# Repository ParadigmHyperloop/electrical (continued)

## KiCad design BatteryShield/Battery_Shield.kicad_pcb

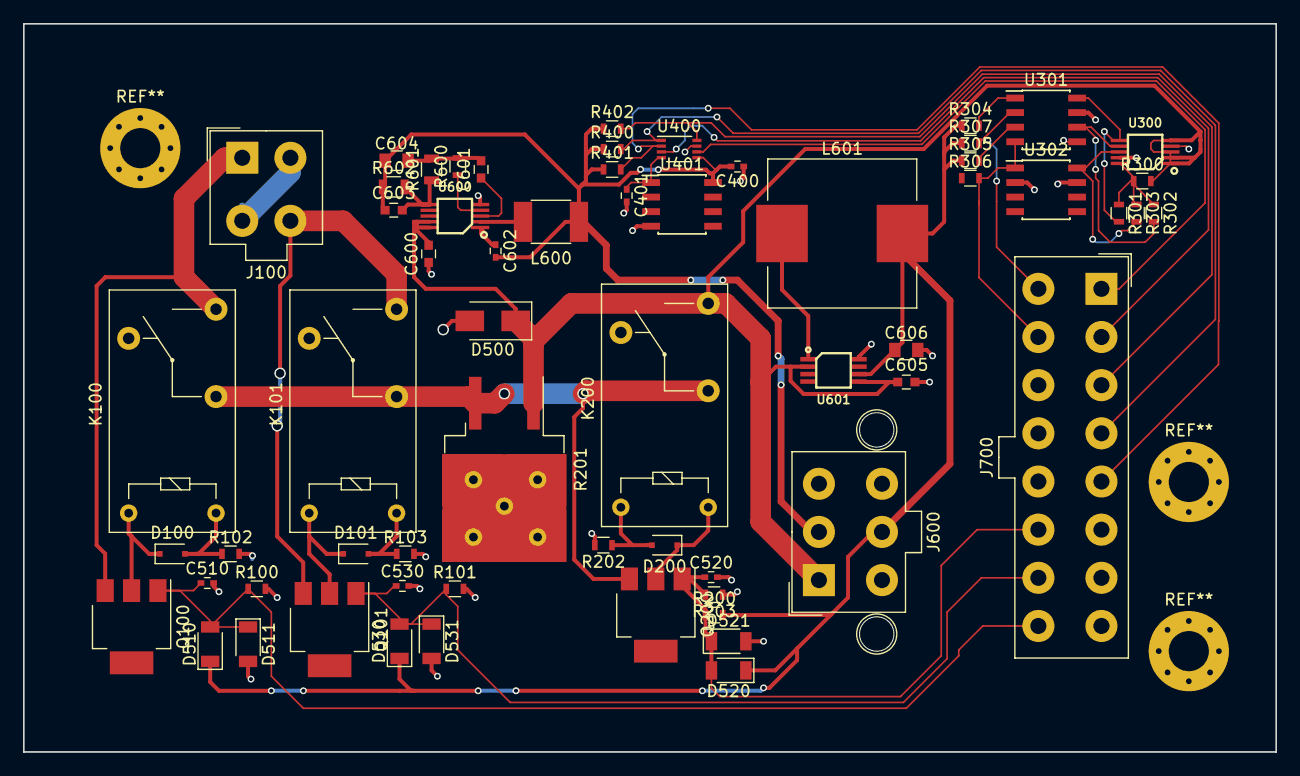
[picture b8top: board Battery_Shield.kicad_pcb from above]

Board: 2 copper layers, 109.2 x 63.5 mm, 62 parts (0 on the bottom side), 38 nets.

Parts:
C400: .1u; C_0402
C401: 10n; C_0402
C510, C520, C530: 10nF; C_0402
C600: 4.7uF; C_0603
C601, C605: 1uF; C_0603
C602: .1uF; C_0402
C603: 10pF; C_0603
C604: 22uF; C_0805
C606: 10uF; C_0805
D100, D101, D200: D; D_SOD-323F
D500: SMAJ36CA; D_SMA
D510, D511, D520, D521, D530, D531: DZ2W03600L; D_1206
J100: Conn_02x02_Counter_Clockwise; Molex_MiniFit-JR-5556-04A_2x02x4.20mm_Straight
J600: Conn_02x03_Counter_Clockwise; Molex_MiniFit-JR-5556-06B_2x03x4.20mm_Straight
J700: MOLEX-MINIFIT-JR-5556; Molex_MiniFit-JR-5556-16A_2x08x4.20mm_Straight
K100, K101, K200: G5LE-14 DC3; Relay_SPDT_OMRON-G5Q
L600: 2.2uH; L_1812
L601: 150uH; L_Wuerth_HCI-1350
Q100, Q101, Q200: ZVP4525G; SOT-223
R100, R101, R102, R103, R200, R202, R203, R400, R401, R402: 1k; R_0603
R201: powerRes; TO-263-2
R300: 0.02; R_0603
R301, R302, R303, R600: 18.2k; R_0603
R304, R305: 0.51k; R_0603
R306, R307: 10k; R_0603
R601: 187K; R_0805
R602: 1M; R_0805
U300: LTC4151IMS-1; MSOP10
U301, U302: MOCD207M; SOIC-8_3.9x4.9mm_Pitch1.27mm
U400: ADC081C021; VSSOP-8_2.3x2mm_Pitch0.5mm
U401: LM35-D; SOIC-8_3.9x4.9mm_Pitch1.27mm
U600: LT8608; MSOP10
U601: LTC3642-3.3; MSOP8

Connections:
3.3V_REG: C606.1, D510.1, D520.1, D530.1, J600.5, L601.2, R200.2, R304.1, R305.1, R306.1, R307.1, U601.6
5V_REG: C400.2, C602.2, C603.1, C604.1, J600.2, L600.1, R400.1, R401.1, R402.1, R602.1, U400.5, U401.8
BBB_GND: C400.1, C401.2, C510.2, C520.2, C530.2, C600.1, C605.2, C606.2, D500.2, D511.2, D521.2, D531.2, J600.3, J600.4, J600.6, J700.6, J700.7, J700.8, J700.11, J700.12, J700.13, R100.2, R101.2, R102.2, R103.2, R202.2, R203.1, U300.4, U300.9, U301.5, U301.7, U302.2, U302.7, U400.7, U401.4, U600.5, U601.8
CV_SCL_BBB: J700.9, R307.2, U301.2
CV_SDA_BBB: J700.10, R306.2, U301.4, U302.1
unnamed: C401.1, U400.4, U401.1
unnamed: C601.1, U600.3
unnamed: C601.2, C604.2, R600.2, R601.2
unnamed: C602.1, U600.1
unnamed: C603.2, R601.1, R602.2, U600.6
unnamed: D100.1, K100.5, Q100.2
unnamed: D100.2, K100.1, R102.1
unnamed: D101.1, K101.5, Q101.2
unnamed: D101.2, K101.1, R103.1
unnamed: D200.1, K200.1, Q200.2
unnamed: D200.2, K200.5, R202.1
unnamed: J100.1, K100.3, Q100.3
unnamed: J100.2, J100.3
unnamed: J100.4, K101.3, Q101.3
unnamed: L600.2, U600.2
unnamed: L601.1, U601.1
unnamed: R300.1, R301.1, R302.1, R303.1, U300.10
unnamed: R301.2, U300.6, U301.8
unnamed: R302.2, U300.7, U301.6
unnamed: R303.2, U300.8, U302.8
unnamed: R304.2, U301.1
unnamed: R305.2, U301.3
unnamed: R600.1, U600.4
PACK_A_ON_N: C510.1, D510.2, D511.1, J700.16, Q100.1, R100.1
PACK_B_ON_N: C530.1, D530.2, D531.1, J700.15, Q101.1, R101.1
PRECHARGE_N: C520.1, D520.2, D521.1, J700.14, Q200.1, R200.1, R203.2
TEMP_DIN_BBB: J700.5, R401.2, U400.2
TEMP_SCL_BBB: J700.4, R400.2, U400.1
TEMP_SDA_BBB: J700.3, R402.2, U400.8
TEMP_SLAVE_ADDR0: J700.2, U400.3
TEMP_SLAVE_ADDR1: J700.1, U400.6
V_BATT37: C600.2, C605.1, D500.1, J600.1, K200.3, R201.1, R300.2, U300.1, U300.2, U300.3, U300.5, U600.9, U600.10, U601.2, U601.5
V_BATT37_PC: K100.2, K101.2, K200.2, Q200.3, R201.3

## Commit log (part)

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2016-12-23 LED Board
    Added the updated LED board with a fairly final PCB layout. It also contains the conditioning circuit for merkl's board for the PSI indicator because there is no more room on his board.
2016-12-26 Revised dimensions of Battery Board to 2.5in x 5.5in. Began layout mostly from scratch because previous revision was not good.
2016-12-27 Completed layout for Battery Board. TODO: DFM Checks
2016-12-28 Committing changes from Luke on MotherBoard
2016-12-31 Full Motherboard Rev1 -- sent for fab
2016-12-31 Minor changes to EmergencyBoard
2017-01-02 Add Correct Motherboard to git
2017-01-03 Finished schematic for SolidStateRelayBoard
2017-01-04 Completed most of layout for SSR board.
2017-01-08 Updated battery board and SSR Board. Completed schematic and layout for Pusher Protection Board (and also renamed it from Emergency Board).
2017-01-08 Corrected problem with Pusher Protection Board. Updated both schematic and layout and regenerated and zipped Gerbers. Ready for fab.
2017-01-12 Motherboard R 1-2
2017-01-12 added Gerbers
2017-01-12 Gerbers should be here now
2017-01-18 Forgot some digikey P/N s
2017-03-29 Tutorial up to board layout complete...Proofread 3/29/2017
2017-04-17 Updated Root Layout Schematic
    - Changed the layout to a modular design like the newer schematics.
    - Added 9th 24V Rail
    - Added 2nd 5v Rail
2017-05-02 Adding Changes to the SSR Board such as a change on the PCB allocating for the correct amount of channels as well as adding the control circuitry for the MPYE’s to the schematic. So changes on the: s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
2017-05-08 Added the LED driver IC to the schematic and started making the changes necessary to the PCB
2017-05-10 Fixed grounding of bat output and connected missing ground connection on LTC chip
2017-05-17 Added the xtr117 to the schematic but I still need to make the footprint for it since the one on kicad is wrong.
2017-05-17 changed to ppm
2017-05-17 Small Misc Changes
2017-05-27 Updated THBO to Rev2
    -Split the board into two parts to allow for better placement on the
    pod.
    -Added LEDs to 5V line
    -Added pin headers at the input terminals to easily put the board into
    self-reference mode using jumpers
    -Changed Vref from 0.64V to 1.25V
2017-05-29 SSR Board
    Misc small changes
2017-05-29 SSR Board
    Small changes to PCB
2017-05-30 SSR Board
    Added Part numbers and links
2017-05-31 MotherfuckingEE
2017-06-02 Made Changes to LED board and SSR
    Added different 5V regulators and polished SSR
2017-06-12 THBO BOM Update, MPB GPIO Schematic
    THBO
    - Updated a few componets parameter values for BOM
    - Created BOM for the board
    MPB
    - Created Schematic for GPIO Circuit to control regulators
2017-06-13 Moving along
2017-06-20 Silk screen mods
2017-06-23 Made a Print
    Just made a PDF
2017-06-27 Added gerbers for THBO
2017-06-28 Updated Silkscreens and added BBB_INT to J106
2017-07-06 Final edits -- awaiting review before sending out
2017-07-06 computer is dying
2017-07-07 XTR111
    Added the xtr111 circuit
2017-07-09 Big Changes to the SSR Board
    Almost finished with the SSR Board. Added the xtr 111 circuits and made
    the layout much cleaner.
2017-07-09 small change on pcb
    mounting holes were messed up
2017-07-10 Finished SSR Board rev 2.1.1
    Updatessss
2017-07-10 weird saved file
2017-07-10 Small Changes
2017-07-10 Small changes to SSR
    Merkl Pls Look
2017-07-11 Rev 2 of battery boards: includes a current sense resistor, pre-charge FET w/ timer, and main FET w/ timer
2017-07-11 Made new Gerbers and PDFs
2017-07-13 Ed please help
2017-07-13 Finished adding footprints; roughly placed all components
2017-07-14 Fixed minor error in Main FET timing circuit
2017-07-15 Updated silkscreen; optimized current consumption; added subcircuit simulations
2017-07-15 Cleaned up some routing; generated Gerbers
2017-07-17 Fixed component footprints; finalized silkscreen; output Gerbers
2017-07-24 Final BOM
2017-07-26 Added the Final BOM
2017-07-26 Initial Changes to LED Board
2017-07-27 Changes as pef discussed with Chris
2017-07-29 Added changes as per Chris requests
2017-07-29 Updated 1M resistors to 2M based on component availability
2017-07-30 Pushing up James' changes
2017-07-30 Adding docs
2017-07-31 Added Digikey PN and Mfg. PN
2017-08-02 Mobo Version 2.1 Added Silk scren Ground Plane Cleanup Pinout changes on Beaglebone Headers, need to modify cabeling from V2.0 and earlier Added power sequencing for ADCs Removed Y3 ADC Removed TI Ba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
2017-08-03 comitted a git sin. thx matan
2017-08-04 Updating to kiCAD version 4.0.6. Updated some .drl files per advanced circuits hold order
2017-08-14 Changed op amp out for comparator (TLV1701).
2017-09-14 Add Photosensors / #ir-detector boards to Git
2017-09-19 Add README for IRDetectors
2017-10-03 updating tag to closeout
2017-10-03 Add "How to burn bootloaders" howto
2017-10-13 Initial pass at automated SVG, PDF, and Gerber exports
2017-10-13 Fetch from origin before attempting to diff against master
2017-10-13 Revert changes from bos-kicad-01
2017-10-13 Archive Plots at end of run, twiddle IRDetector PCB to test
2017-10-13 Run #electrical nodes on remote KiCAD build slave
2017-10-13 Tests Succeeded: Revert back IRDetectors/PhotoSensors.kicad_pcb
2017-10-13 Triggering another build
2017-11-03 added files
2017-11-03 organized more
2017-11-05 added connectors footprints and .libs from other boards
2017-11-05 cmnt
2017-11-07 added solder pad to connectors
2017-11-13 Structured into Paradigm Modules/Libraries
2017-11-15 layout reorganzied, before SMD molex
2017-11-16 Fixed Connectors,pretty
2017-11-17 removed Diods.lib, Capacitor.pretty, and Connectors.pretty
2017-11-26 created branch to start work on BB-CompIII
2018-01-11 Initial commit for test board. Added DAC7578.
2018-01-16 added 3V3 pour and 24V cutout. Filled GND plane and made AGND cutout. SERCOM for SOL & DAC needs some cleaning. Routed SOL outputs
2018-01-17 fixed folder labyrinth
2018-01-17 Added a readme for to help with setting up Eeschema for the first time. It didn't work well in the template itself.
2018-01-17 Updated readme to include directions on adding the template to the test project.
2018-01-17 Travis and gitignore for firmware
2018-01-19 Cleaned up connections and labels in sketch.
2018-01-21 Making sure PCB changes are on git since last push
2018-01-21 Battery Shield project created
    Created hierarchal sheets for us to work on Battery Shield from top-level down.
2018-01-21 All of rat's nest satisfied except for SOL spi line
2018-01-23 Fixing folder/adding schematics to hierarchal sheet
2018-01-24 Added Full Wilson Current Mirror
2018-01-26 added instrumentation amplifier
2018-01-29 Fixed all incorrect trace size issues. Passed DRC. Added extra 5V header. Began labeling connectors with human readble names. Changed all through hole GND pins to rectangular pads instead of circular
2018-01-31 Adding .gitignore to ignore .bak and -bak files.
2018-01-31 Added testpoints and silkscreen descriptions to PCB. Added Paradigm template to schematic.
2018-02-01 Directory/.pro cleanup
    Cleanup of .pro and removed CurrentVoltageSensor.pro
2018-02-02 Adding instrumentation amplifier circuit
2018-02-03 Adding temperature sensor schematic
2018-02-11 Added some ideas for isolation and an alternate temp sensor
2018-02-18 Cleaning up testing board
2018-02-18 current_sink update
2018-05-28 Preliminary pack selector circuit
    May use power FETs instead of relays. this is a bit complicated
2018-05-30 Added precharge circuit. Also fixed up power pack selector
    Also need to add 12V regulator
2018-05-31 Fixed mistake with relay coil pulldown
    Added pull down to relay coil in pre-charge circuit
2018-06-02 Added two pages, cleaned up net names
    Cleaned up net names. Added protection/grounding and BBB interface socket. Additional work needs to be done with grounding/mounting holes and 37V rail reverse current protection.
2018-06-19 Associated a lot of footprints
    Now I need to add a lot more :(
2018-06-20 All footprints added for gen 1 battery board
    Woot. Layout soon!!!
2018-06-23 Added some small traces
    oops I forgot them originally
2018-06-28 fixed transistors
    Fixed transistor issue with precharge circuit, added some extra optional bom modifications
2018-06-29 Changed BBB regulation voltage from 5V to 3.3V
2018-06-30 fixed driver issue and routing
2018-07-01 Small update
2018-07-20 Updated bom stuff, made new gerbers and added a trace route
    damn,
2018-07-22 Added thermal vias for power resistor
    wow, nice.
2018-07-23 Fixed issue with kicad
2018-09-29 added renders and made 3d things
2018-10-14 Made real gerbers
    Rip
2018-11-04 New cape branch added. BBB cape schematic has USb connector and the GPIO from the BBB.
2018-11-11 Added the MCU
2018-11-12 Me and Frank
    fUCKED SHIT UP
2018-12-01 Battery Input
    Did out some schematic work for the battery inputs, which is lit
2018-12-23 Outputs Finalized
    @Frank got all the outputs we talked about added. Also added nmos for cooling pump, inverter control. Current sensors are next and then DCDCs.
2018-12-24 Inputs / Outputs Reallyyyy Done
    These two schematic sections are very finalized now. Time to do the power conversion section : - )
2018-12-26 Merry Chungus
    Big ~Christmas~ _Chungus_ commit here boys. Rails are UP.
2018-12-26 Schematic "Done"
    -Added Wiznet legacy n0de schematic
    -Cleaned up schematic in general
    -Other than minor changes, the schematic is finalized.
2018-12-28 Rev Protection Fix
    - Added LTspice models of reverse protection.
    - Fixed reverse protection circuit, verified through spice.
    - Added net names to NAP PoE circuit.
2019-02-01 Attempted to clean up LVDC layout slightly
    Moved the the MOSFETs and a few other things around in a (misguided) attempt to make it cleaner.
    I apologize in advance to anyone who looks at this, it's quite a mess.
2019-02-05 LVDC Layout work (see description)
    -Added remaining components, except for Y501 (to be added during routing)
    -Fixed many footprints
    -Rearranged to make screw terminals and fuses fit better
    -I apologize in advance
2019-03-08 Mostly uC schematic updates
    - Added RC filter on RESET
    - Added optional 25MHz crystal
    - Added 1K pullup on SWCLK
2019-03-09 Annotated and references
    Added annotations and references. MCU pins to be added next
2019-03-10 Added population options for power modules
2019-03-10 Filled out footprints and annotated 5V regulator schematic
2019-03-11 layout -wiz-24v
2019-05-04 BMS replacement capacitor drop in board.
2019-05-07 made gerber files and ordered board
2019-05-08 Added some more harnesses
    added shit
2019-05-08 First commit; creating schematic
2019-05-10 added or logic
2019-05-12 minor changes
    bulkheads
2019-05-15 Starting Layout.
2019-05-16 Routing done. Ready for review
2019-05-17 Pushing zip
2019-05-20 Updating wiznet sheet to match ordered silk, gen bom
2019-05-24 Schematic Done and Layout started
2019-05-26 Wiznet circuit done. Not forgetting to commit
2019-05-28 Added sensors
2019-05-28 Half of wiznet is layed out. Fixed PMODE termination resistors.
2019-05-30 Adding template for BeagleCape V2
2019-06-04 Routed on and off board sensors.
2019-06-04 SPI bus connected
2019-06-05 bom uploaded, adjusted silk, ICs spec'd, review rdy
2019-06-06 Finnished routing. Adding analogue connectors
2019-06-09 Fixed silkscreen. Moved I2C bus. ready to order.
2019-06-10 Added wiring for motor side resolver cable.
2019-06-13 Added J1 wiring pinout to inverter side of bulkhead resolver cable.
2019-06-16 added BOM for datboi frank
2019-06-28 upddated RJ45 Bulkhead wiring
2019-07-06 updated to include new signal bulkheads. Still unsure of bb bms CAN wiring
2019-07-06 updated drawing a tad for signal bulkhead
    woot
2019-07-14 Assigned more wires for 1872 connector and listed extras.
